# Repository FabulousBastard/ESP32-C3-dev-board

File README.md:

# ESP32-C3-dev-board

does not work
  - get's power 
  - isn't recognized by Windows
  
 possibel reasons 
  - soldering error
  - PCB design 
  - wong part's selection 
  - software issue

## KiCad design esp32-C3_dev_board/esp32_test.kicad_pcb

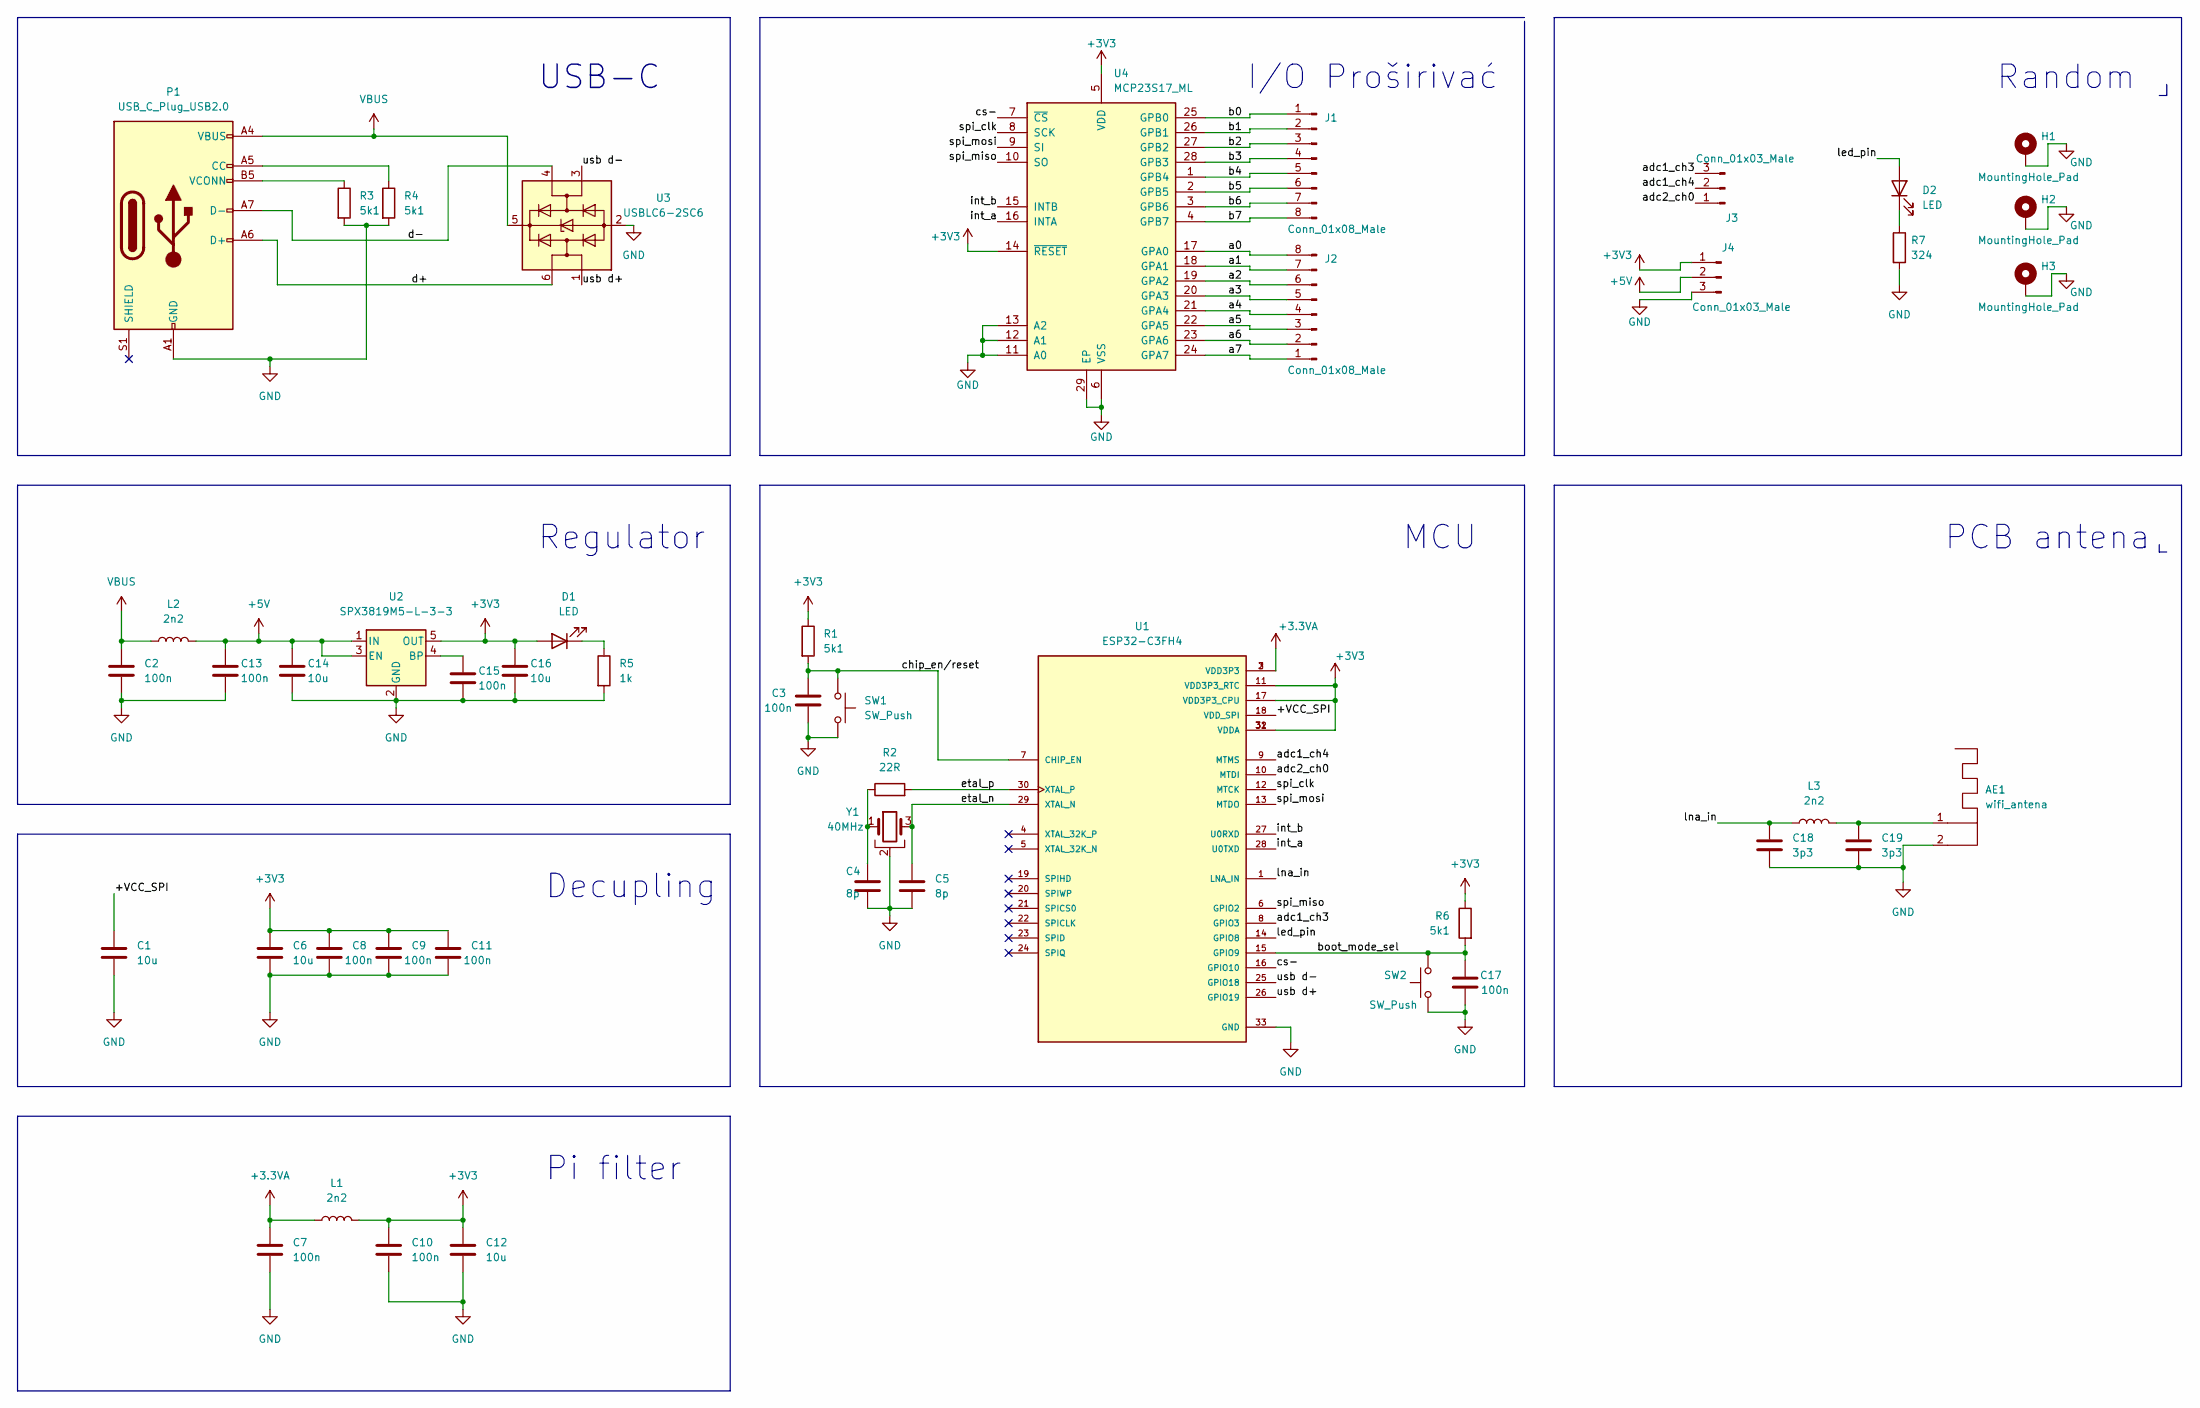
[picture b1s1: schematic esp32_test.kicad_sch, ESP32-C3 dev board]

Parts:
AE1: wifi_antena
C1: 10u; C_0603_1608Metric
C2, C3, C7, C8, C9, C10, C11, C13, C15, C17: 100n; C_0402_1005Metric_Pad0.74x0.62mm_HandSolder
C4, C5: 8p; C_0402_1005Metric_Pad0.74x0.62mm_HandSolder
C6, C12, C14, C16: 10u; C_0603_1608Metric_Pad1.08x0.95mm_HandSolder
C18, C19: 3p3; C_0402_1005Metric_Pad0.74x0.62mm_HandSolder
D1, D2: LED; LED_0603_1608Metric_Pad1.05x0.95mm_HandSolder
H1, H2, H3: MountingHole_Pad; MountingHole_2.2mm_M2_Pad
J1, J2: Conn_01x08_Male; PinHeader_1x08_P2.54mm_Vertical
J3, J4: Conn_01x03_Male; PinHeader_1x03_P2.54mm_Vertical
L1, L2, L3: 2n2; L_0603_1608Metric_Pad1.05x0.95mm_HandSolder
P1: USB_C_Plug_USB2.0; USB_C_Receptacle_JAE_DX07S016JA1R1500
R1, R3, R4, R6: 5k1; R_0402_1005Metric_Pad0.72x0.64mm_HandSolder
R2: 22R; R_0402_1005Metric_Pad0.72x0.64mm_HandSolder
R5: 1k; R_0402_1005Metric_Pad0.72x0.64mm_HandSolder
R7: 324; R_0402_1005Metric_Pad0.72x0.64mm_HandSolder
SW1, SW2: SW_Push; SW_PUSH_6mm_H5mm
U1: ESP32-C3FH4; QFN50P500X500X90-33N; PARTREV V1.0
U2: SPX3819M5-L-3-3; SOT-23-5
U3: USBLC6-2SC6; SOT-23-6
U4: MCP23S17_ML; QFN-28-1EP_6x6mm_P0.65mm_EP4.25x4.25mm
Y1: 40MHz; Crystal_SMD_2520-4Pin_2.5x2.0mm

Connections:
+3.3VA: C7.1, L1.1, U1.2 (VDD3P3), U1.3 (VDD3P3)
+3V3: C6.1, C8.1, C9.1, C10.1, C11.1, C12.1, C16.1, D1.2 (A), J4.1, L1.2, R1.1, R6.1, U1.11 (VDD3P3_RTC), U1.17 (VDD3P3_CPU), U1.31 (VDDA), U1.32 (VDDA), U2.5 (OUT), U4.5 (VDD), U4.14 (~RESET)
+5V: C13.1, C14.1, J4.2, L2.2, U2.1 (IN), U2.3 (EN)
/+VCC_SPI: C1.1, U1.18 (VDD_SPI)
/a0: J2.8, U4.17 (GPA0)
/a1: J2.7, U4.18 (GPA1)
/a2: J2.6, U4.19 (GPA2)
/a3: J2.5, U4.20 (GPA3)
/a4: J2.4, U4.21 (GPA4)
/a5: J2.3, U4.22 (GPA5)
/a6: J2.2, U4.23 (GPA6)
/a7: J2.1, U4.24 (GPA7)
/adc1_ch3: J3.3, U1.8 (GPIO3)
/adc1_ch4: J3.2, U1.9 (MTMS)
/adc2_ch0: J3.1, U1.10 (MTDI)
/b0: J1.1, U4.25 (GPB0)
/b1: J1.2, U4.26 (GPB1)
/b2: J1.3, U4.27 (GPB2)
/b3: J1.4, U4.28 (GPB3)
/b4: J1.5, U4.1 (GPB4)
/b5: J1.6, U4.2 (GPB5)
/b6: J1.7, U4.3 (GPB6)
/b7: J1.8, U4.4 (GPB7)
/boot_mode_sel: C17.1, R6.2, SW2.2, U1.15 (GPIO9)
/chip_en/reset: C3.1, R1.2, SW1.1, U1.7 (CHIP_EN)
/cs-: U1.16 (GPIO10), U4.7 (~CS)
/d+: P1.A6 (D+), U3.6 (I/O1)
/d-: P1.A7 (D-), U3.4 (I/O2)
/etal_n: C5.1, U1.29 (XTAL_N), Y1.3
/etal_p: R2.2, U1.30 (XTAL_P)
/int_a: U1.28 (U0TXD), U4.16 (INTA)
/int_b: U1.27 (U0RXD), U4.15 (INTB)
/led_pin: D2.2 (A), U1.14 (GPIO8)
/lna_in: C18.1, L3.1, U1.1 (LNA_IN)
/spi_clk: U1.12 (MTCK), U4.8 (SCK)
/spi_miso: U1.6 (GPIO2), U4.10 (SO)
/spi_mosi: U1.13 (MTDO), U4.9 (SI)
/usb d+: U1.26 (GPIO19), U3.1 (I/O1)
/usb d-: U1.25 (GPIO18), U3.3 (I/O2)
GND: AE1.2, C1.2, C2.2, C3.2, C4.2, C5.2, C6.2, C7.2, C8.2, C9.2, C10.2, C11.2, C12.2, C13.2, C14.2, C15.2, C16.2, C17.2, C18.2, C19.2, H1.1, H2.1, H3.1, J4.3, P1.A1 (GND), P1.A12 (GND), P1.B1 (GND), P1.B12 (GND), R3.2, R4.2, R5.2, R7.2, SW1.2, SW2.1, U1.33 (GND), U1.34, U1.35, U1.36, U1.38, U1.40, U1.41, U1.42, U1.43, U1.45, U1.47, U1.48, U1.49, U2.2 (GND), U3.2 (GND), U4.6 (VSS), U4.11 (A0), U4.12 (A1), U4.13 (A2), U4.29 (EP), Y1.2, Y1.4
unnamed: AE1.1, C19.1, L3.2
unnamed: C4.1, R2.1, Y1.1
unnamed: C15.1, U2.4 (BP)
unnamed: D1.1 (K), R5.1
unnamed: D2.1 (K), R7.1
unnamed: P1.A5 (CC), R4.1
unnamed: P1.B5 (VCONN), R3.1
VBUS: C2.1, L2.1, P1.A4 (VBUS), P1.A9 (VBUS), P1.B4 (VBUS), P1.B9 (VBUS), U3.5 (VBUS)

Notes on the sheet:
Decupling
I/O Proširivać
MCU
PCB antena
Random
USB-C
Regulator
Pi filter

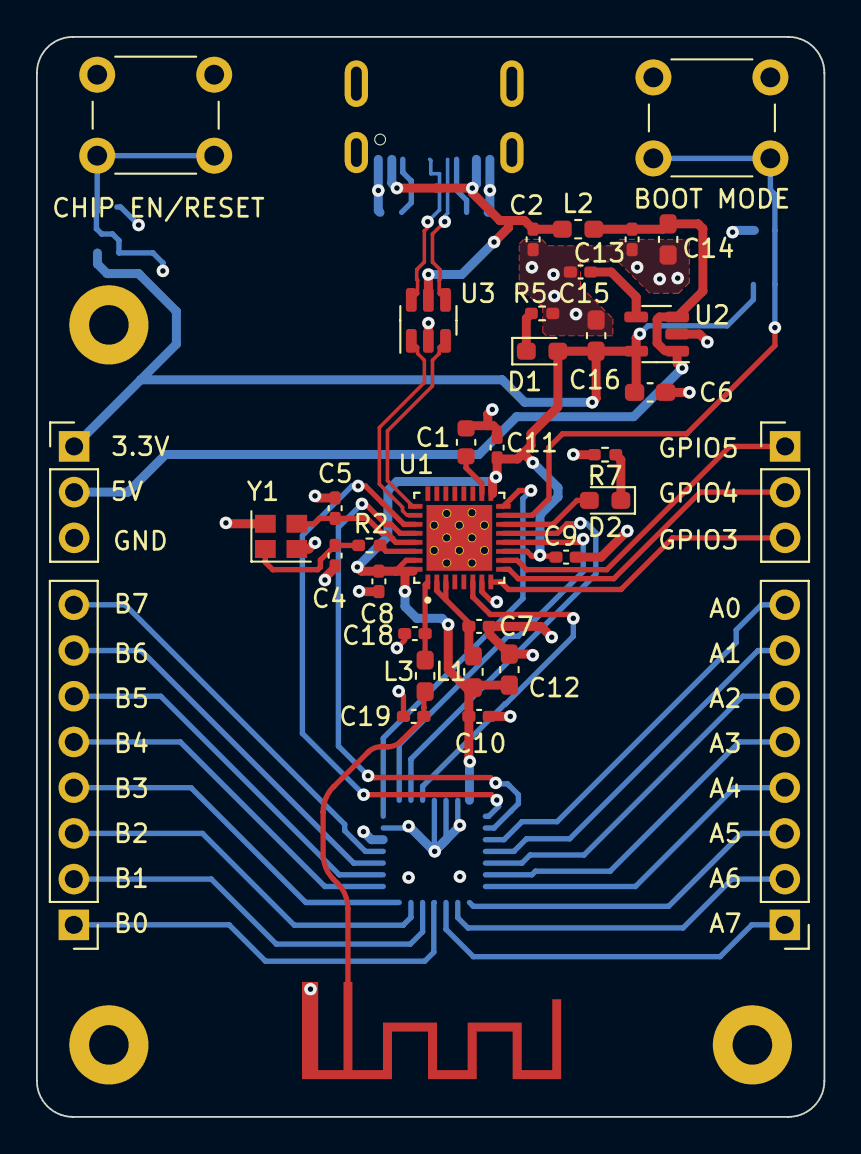
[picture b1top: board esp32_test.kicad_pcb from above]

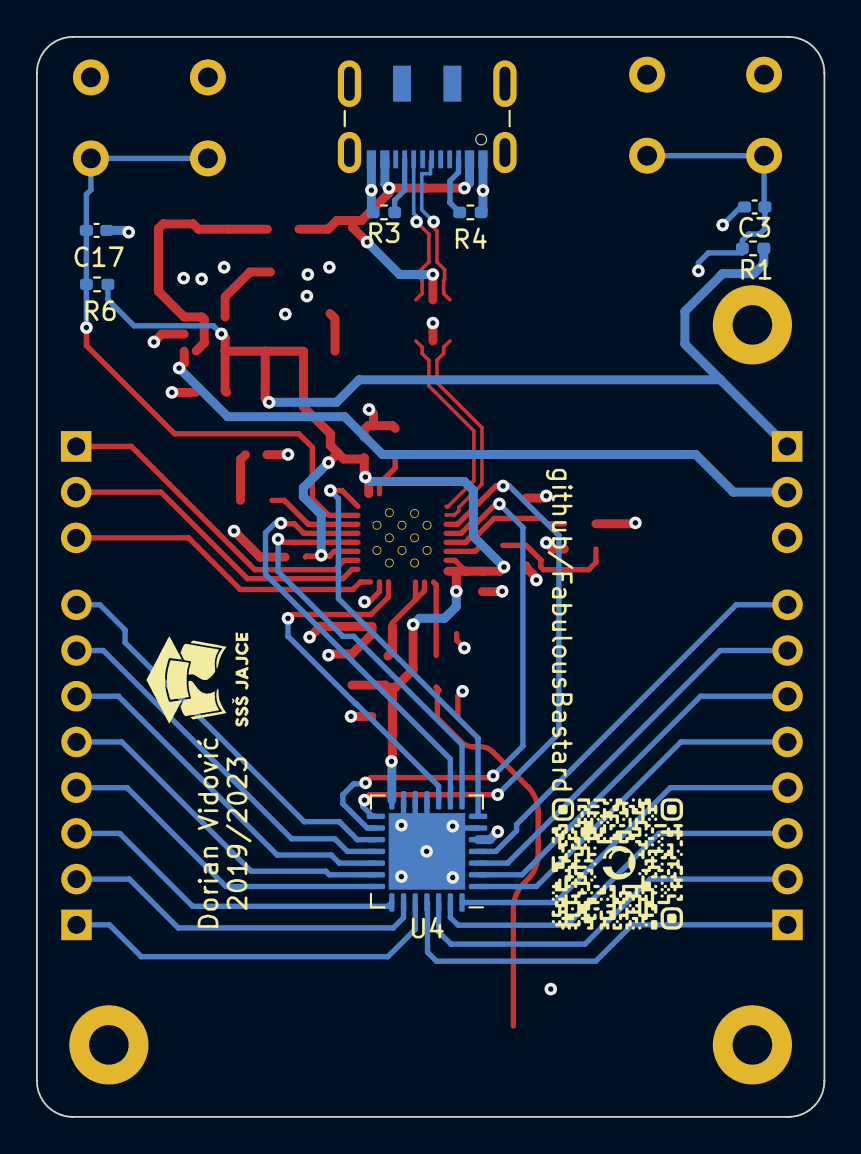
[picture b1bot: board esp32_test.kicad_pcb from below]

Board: 4 copper layers, 43.8 x 60.0 mm, 47 parts (8 on the bottom side), 48 nets.

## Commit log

2023-02-15 Rename LICENSE.markdown to LICENSE.md
